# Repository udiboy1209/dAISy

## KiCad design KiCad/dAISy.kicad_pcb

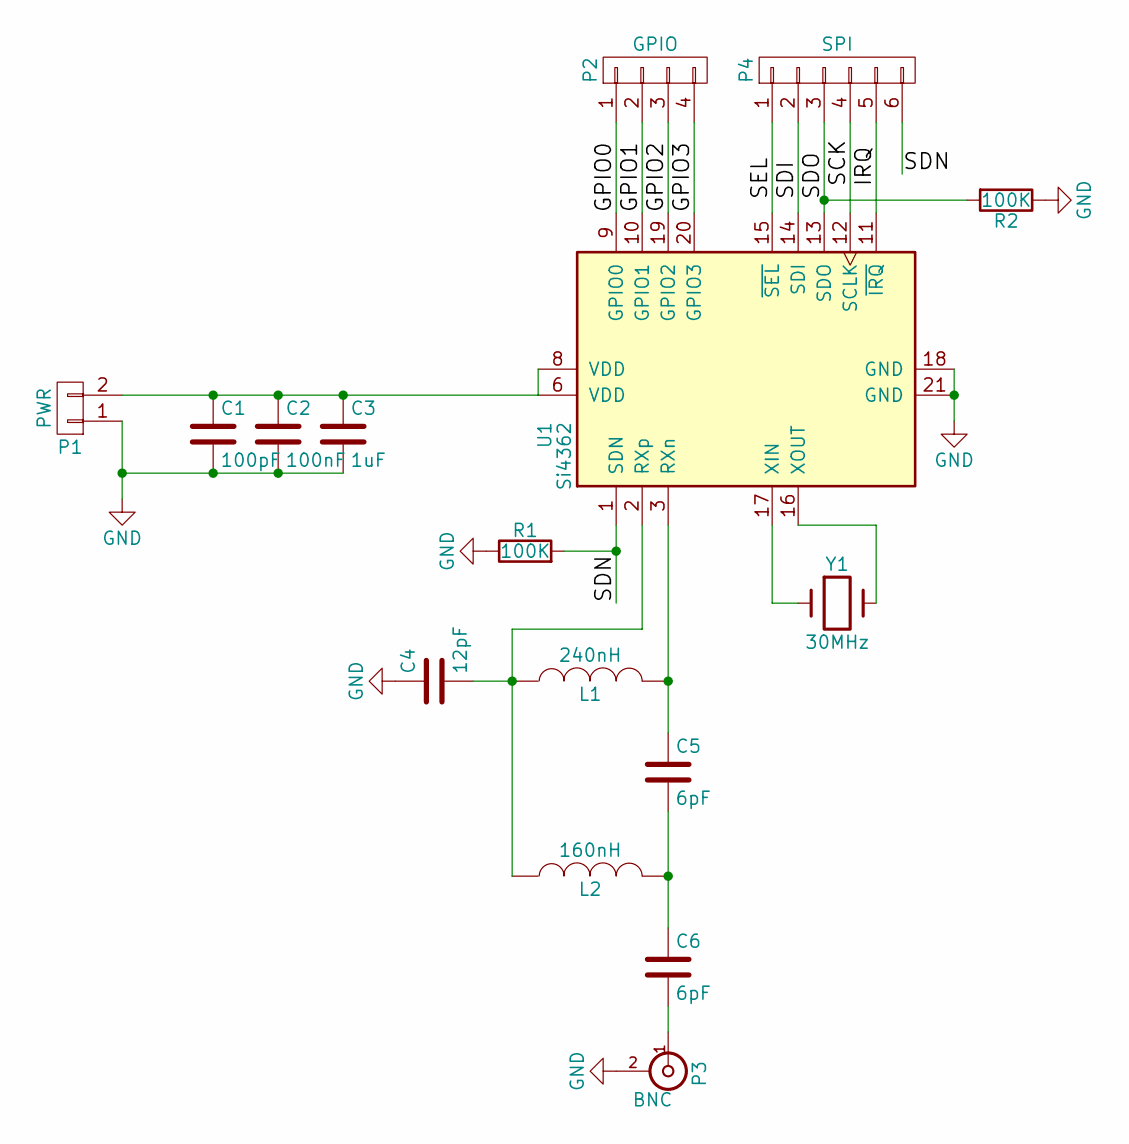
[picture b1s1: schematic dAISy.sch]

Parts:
C1: 100pF; C_Disc_D3_P2.5
C2: 100nF; C_Disc_D3_P2.5
C3: 1uF; C_Disc_D3_P2.5
C4: 12pF; C_Disc_D3_P2.5
C5, C6: 6pF; C_Disc_D3_P2.5
L1: 240nH; Resistor_Horizontal_RM10mm
L2: 160nH; Resistor_Horizontal_RM10mm
P1: PWR; Pin_Header_Straight_1x02
P2: GPIO; Pin_Header_Straight_1x04
P3: BNC; BNC_Socket_TYCO-AMP_LargePads
P4: SPI; Pin_Header_Straight_1x06
R1, R2: 100K; Resistor_Horizontal_RM7mm
U1: Si4362; QFN-20-1EP_4x4mm_Pitch0.5mm
Y1: 30MHz; Crystal_HC49-U_Vertical

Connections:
/GPIO0: P2.1, U1.9 (GPIO0)
/GPIO1: P2.2, U1.10 (GPIO1)
/GPIO2: P2.3, U1.19 (GPIO2)
/GPIO3: P2.4, U1.20 (GPIO3)
/IRQ: P4.5, U1.11 (~IRQ)
/SCK: P4.4, U1.12 (SCLK)
/SDI: P4.2, U1.14 (SDI)
/SDN: P4.6, R1.2, U1.1 (SDN)
/SDO: P4.3, R2.2, U1.13 (SDO)
/SEL: P4.1, U1.15 (~SEL)
GND: C1.2, C2.2, C3.2, C4.1, P1.1, P3.2 (Ext), R1.1, R2.1, U1.18 (GND), U1.21 (GND)
unnamed: C1.1, C2.1, C3.1, P1.2, U1.6 (VDD), U1.8 (VDD)
unnamed: C4.2, L1.1, L2.1, U1.2 (RXp)
unnamed: C5.1, L1.2, U1.3 (RXn)
unnamed: C5.2, C6.1, L2.2
unnamed: C6.2, P3.1 (In)
unnamed: U1.16 (XOUT), Y1.2
unnamed: U1.17 (XIN), Y1.1

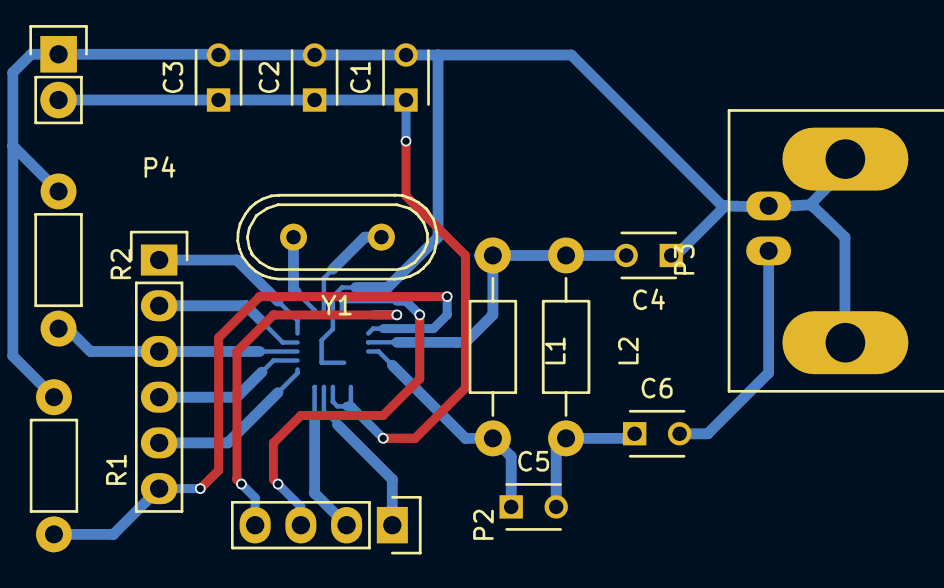
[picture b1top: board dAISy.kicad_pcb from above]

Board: 2 copper layers, 16 parts (1 on the bottom side), 18 nets.

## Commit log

2017-12-05 Create PCB with DIP components
